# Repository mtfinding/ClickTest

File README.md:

# Automated Continuity Testing Device

## Overview

This repository contains the finalized source-code and hardware design documents of an automated hardware-tester. The projects was created as part of bachelor-thesis and is specifically designed for the Nucleo L432KC development board in combination with a propriatory harwdare expander used at my uni FHTW)  
## Features

- **Automated Continuity Testing**: The device automates the continuity testing process, reducing manual effort and increasing efficiency.
- **Terminal Interface**: A 115200baud UART terminal is available to visulaize test-results and select from certain testing-options.
- **Quick-Test Button**: A physical button that can be mapped to various test-actions via terminal commands.

## System overview

The system consists of a single PCBA project which can be broken apart in all necessary components with only little manual THT soldering required.
The main components are outlined in the image below.

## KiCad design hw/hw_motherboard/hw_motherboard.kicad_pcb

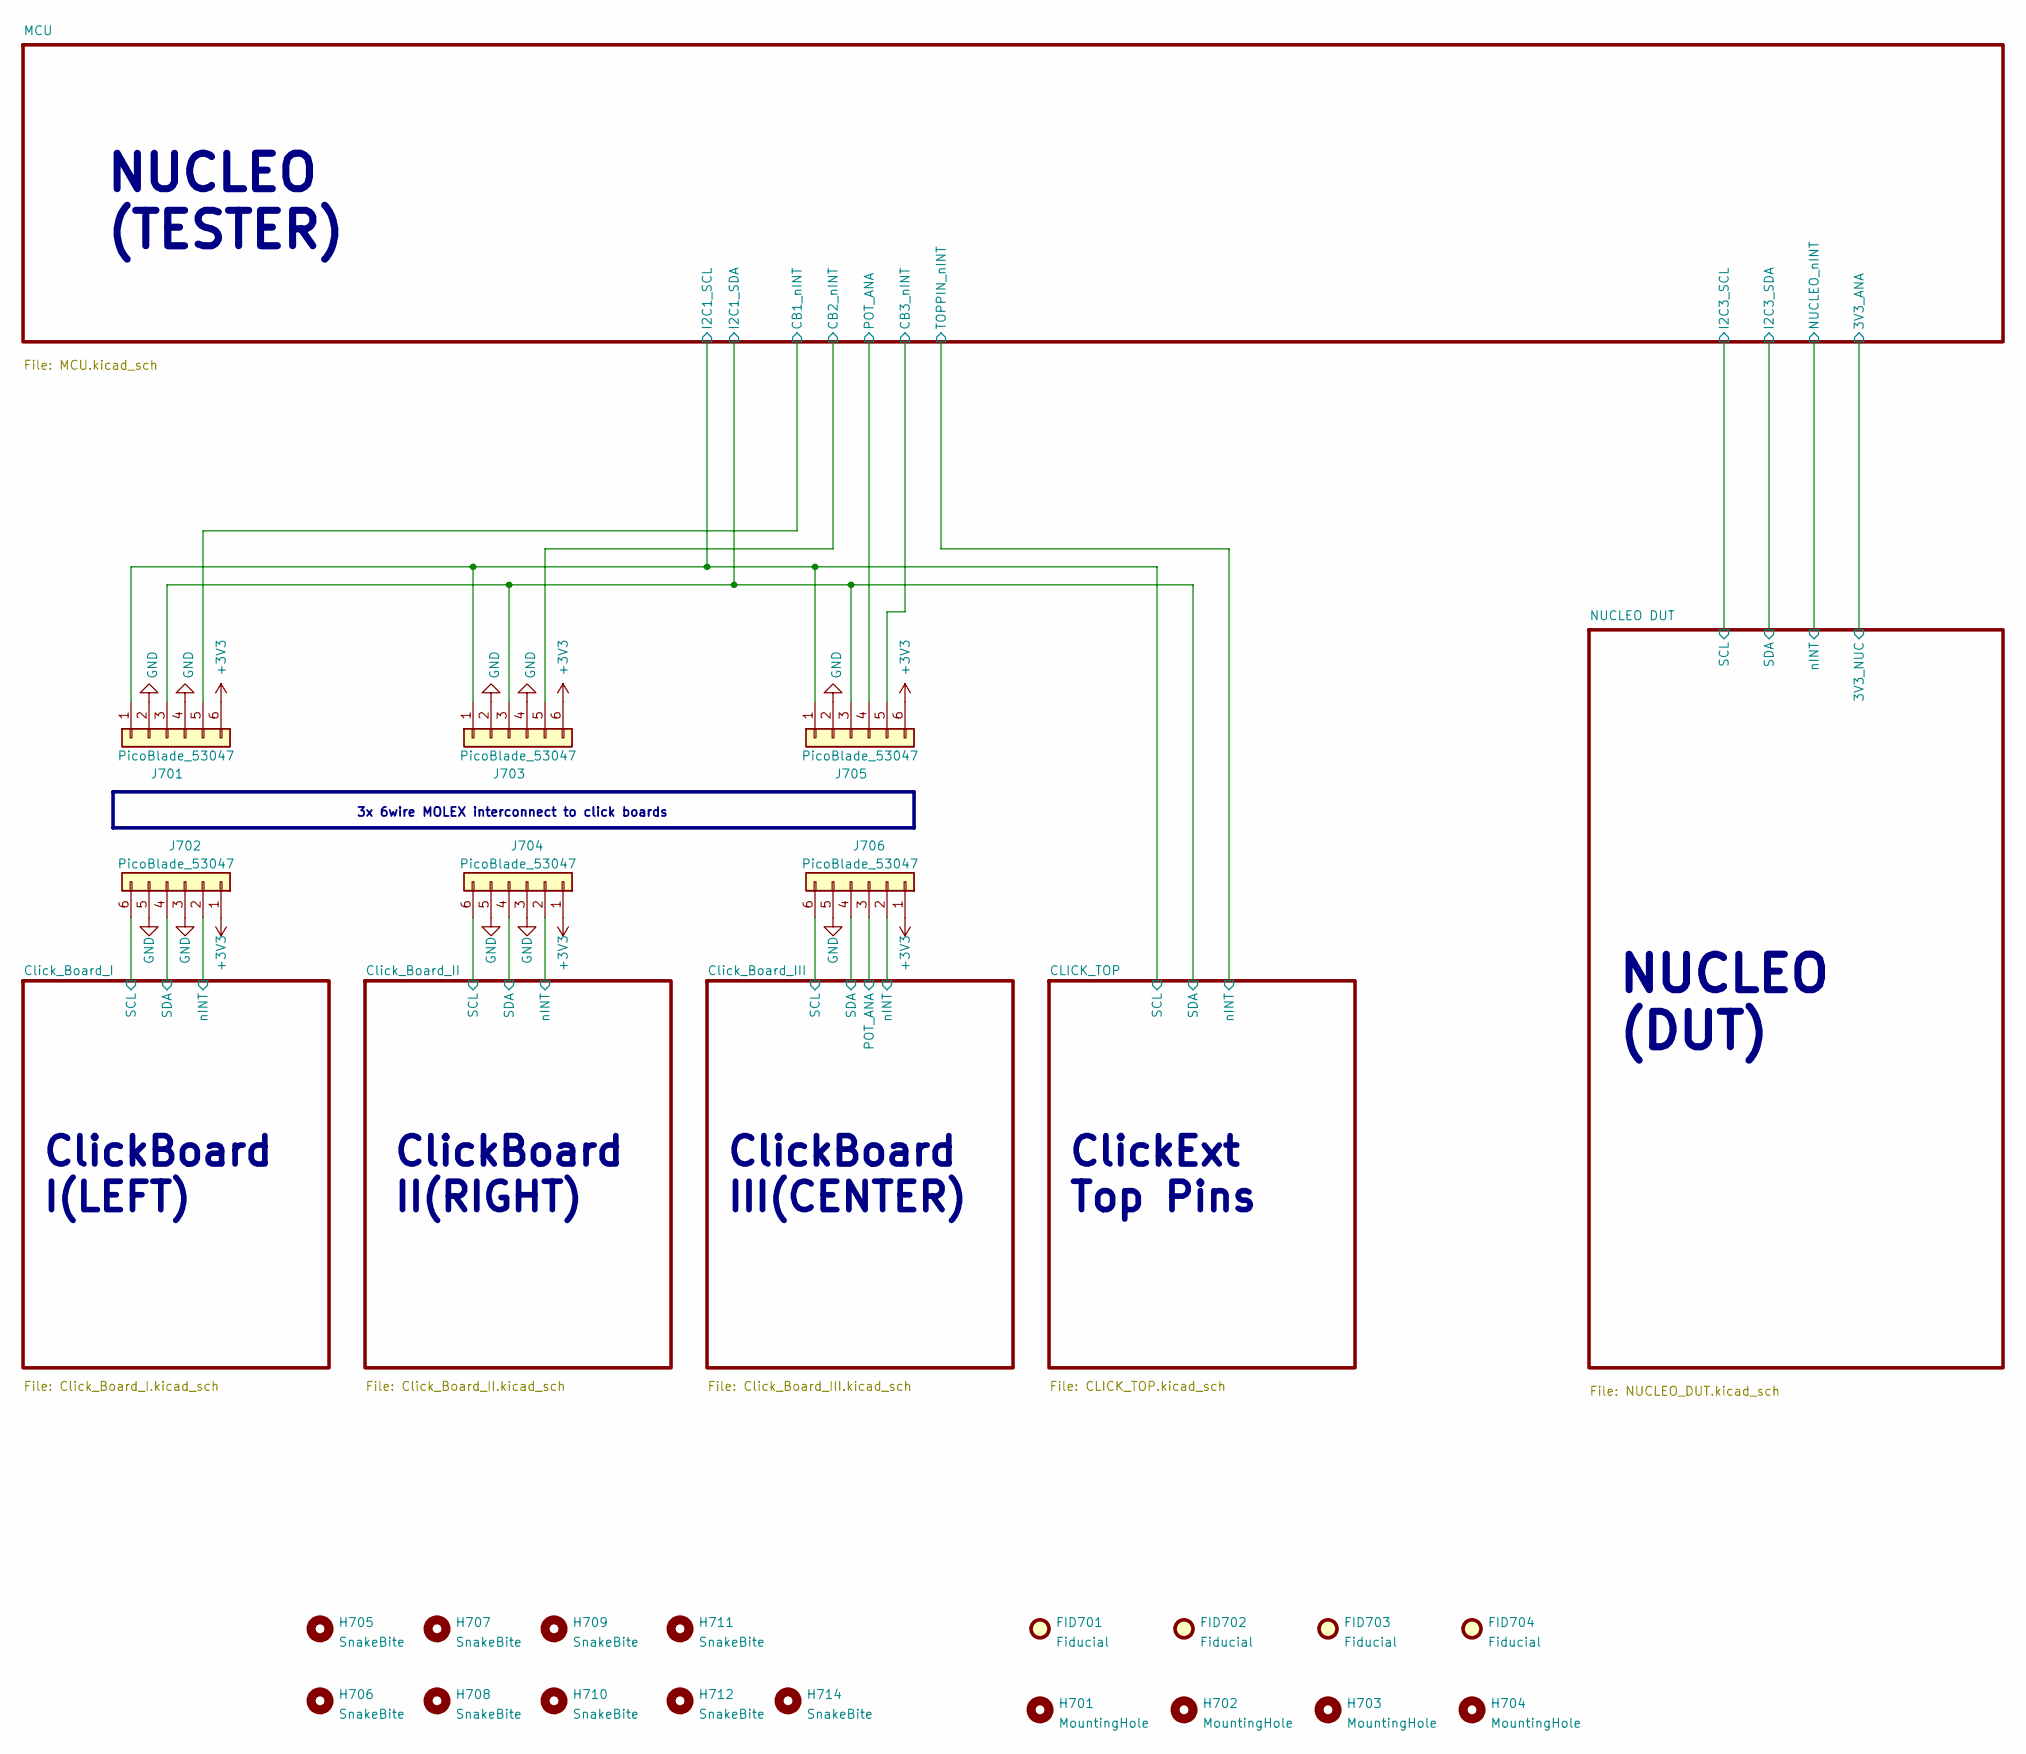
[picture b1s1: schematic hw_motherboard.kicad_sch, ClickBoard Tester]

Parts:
FID701, FID702, FID703, FID704: Fiducial; Fiducial_1mm_Mask2mm
H701, H702, H703, H704: MountingHole; MountingHole_3.2mm_M3_Pad_Via
H705, H706, H707, H708, H709, H710, H711, H712, H714: SnakeBite; JLC_SnakeBite_1.27mm
J701, J702, J703, J704, J705, J706: PicoBlade_53047; Molex_PicoBlade_53047-0610_1x06_P1.25mm_Vertical

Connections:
+3V3: J701.6, J702.1, J703.6, J704.1, J705.6, J706.1; also elsewhere on the board
/Click_Board_I/SCL: J702.6; also elsewhere on the board
/Click_Board_I/SDA: J702.4; also elsewhere on the board
/Click_Board_I/nINT: J702.2; also elsewhere on the board
/Click_Board_II/SCL: J704.6; also elsewhere on the board
/Click_Board_II/SDA: J704.4; also elsewhere on the board
/Click_Board_II/nINT: J704.2; also elsewhere on the board
/Click_Board_III/POT_ANA: J706.3; also elsewhere on the board
/Click_Board_III/SCL: J706.6; also elsewhere on the board
/Click_Board_III/SDA: J706.4; also elsewhere on the board
/Click_Board_III/nINT: J706.2; also elsewhere on the board
/MCU/MCU_PA9: J701.1, J703.1, J705.1; also elsewhere on the board
/MCU/MCU_PA10: J701.3, J703.3, J705.3; also elsewhere on the board
/MCU/MCU_PB6: J701.5, J703.5, J705.5; also elsewhere on the board
/MCU/POT_ANA: J705.4; also elsewhere on the board
GND: J701.2, J701.4, J702.3, J702.5, J703.2, J703.4, J704.3, J704.5, J705.2, J706.5; also elsewhere on the board

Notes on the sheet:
3x 6wire MOLEX interconnect to click boards
NUCLEO (DUT)
ClickBoard I(LEFT)
ClickExt Top Pins
ClickBoard III(CENTER)
NUCLEO (TESTER)
ClickBoard II(RIGHT)

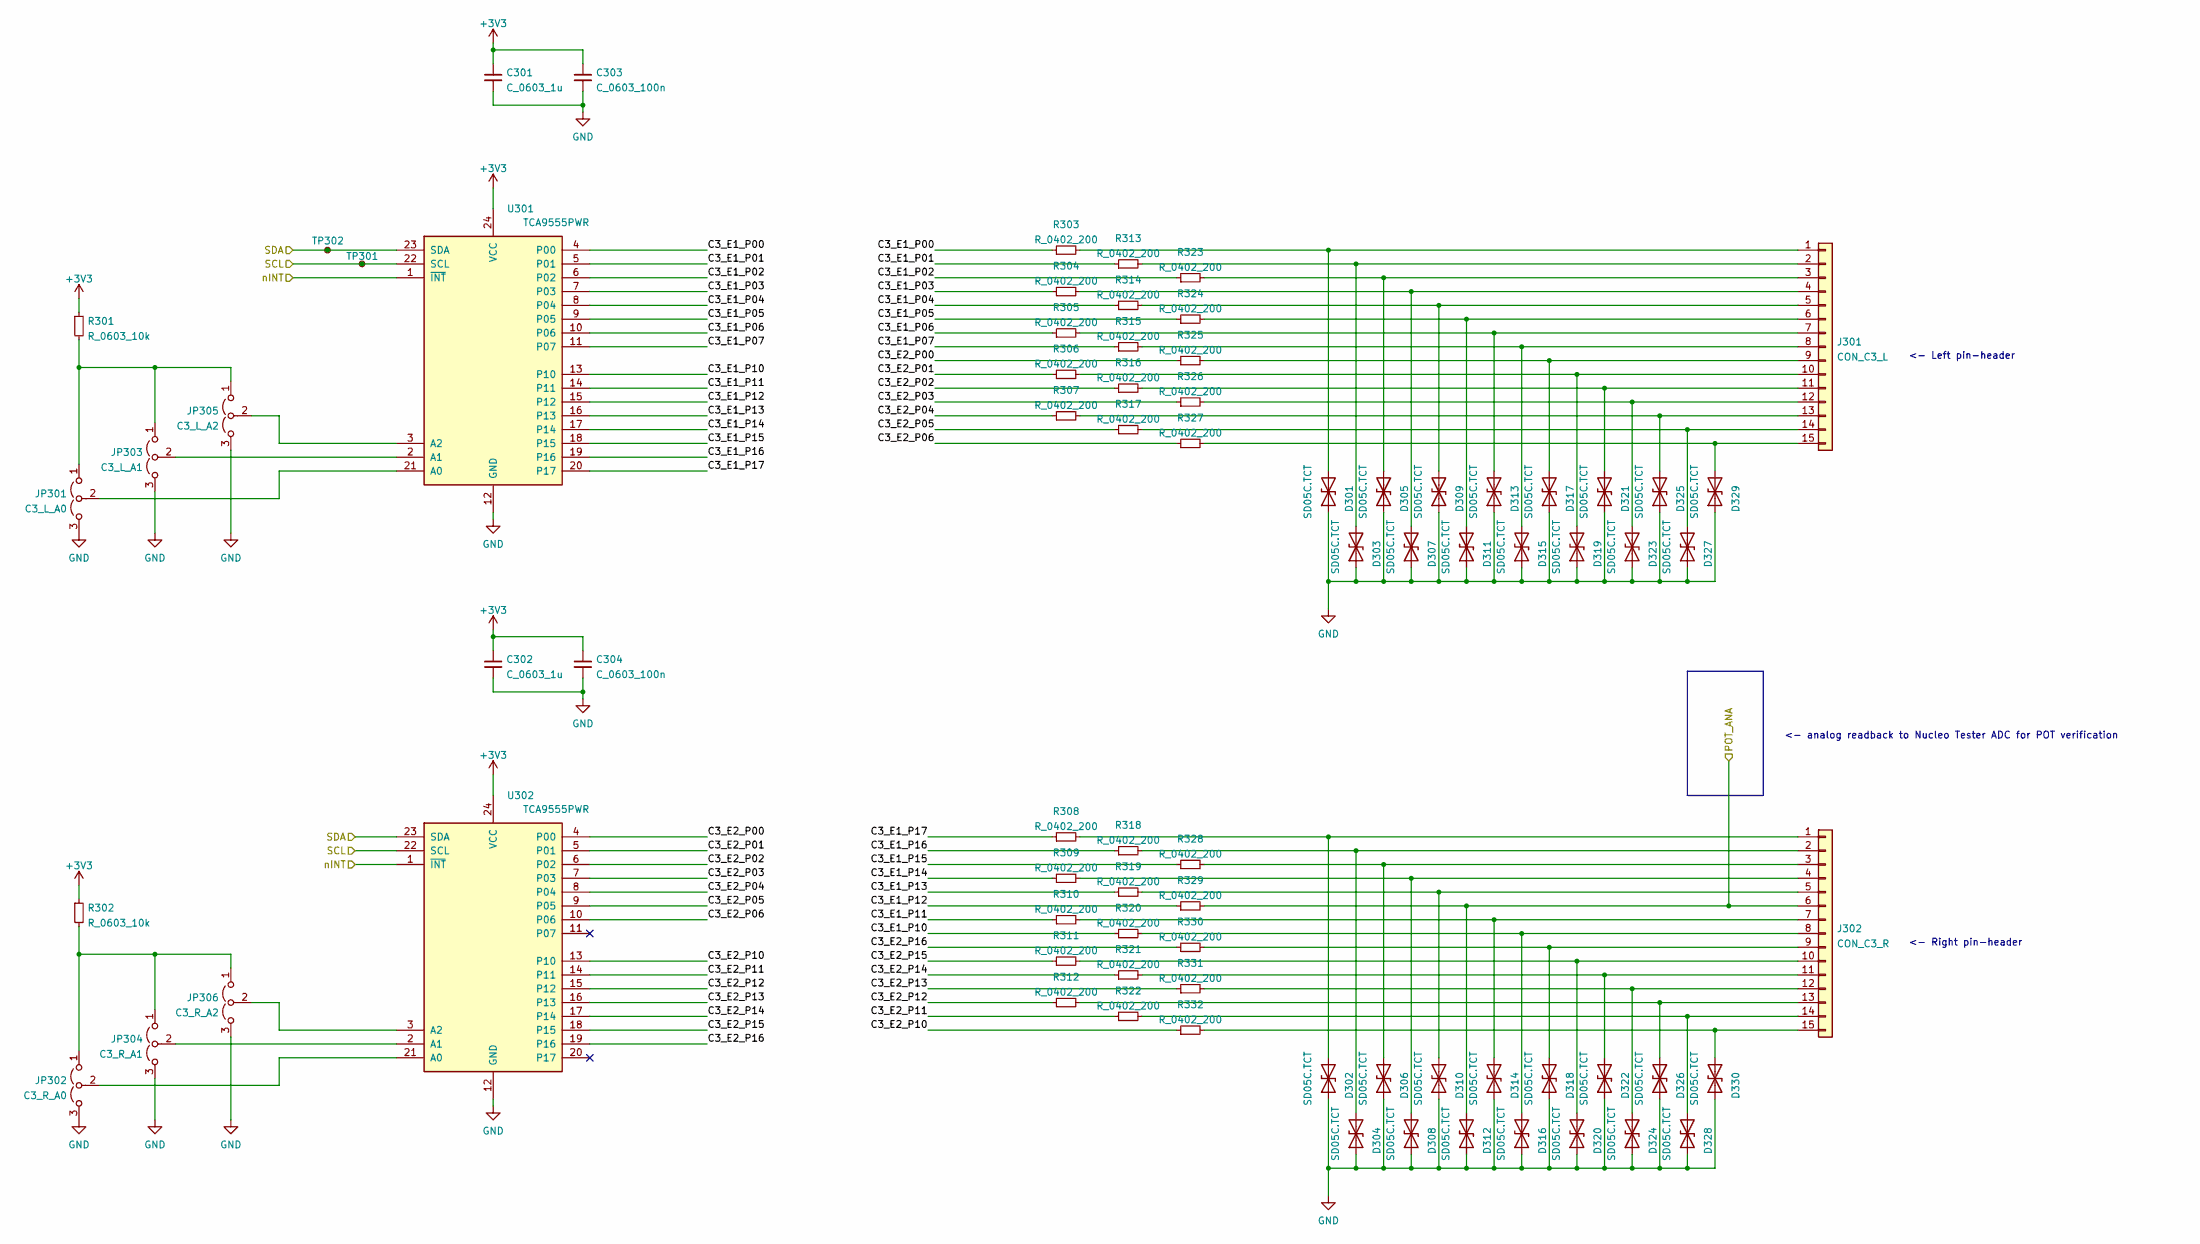
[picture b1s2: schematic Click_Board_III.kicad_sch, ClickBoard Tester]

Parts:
C301, C302: C_0603_1u; C_0603_1608Metric; LCSC Part # C15849
C303, C304: C_0603_100n; C_0603_1608Metric; LCSC Part # C14663
D301, D302, D303, D304, D305, D306, D307, D308, D309, D310, D311, D312, D313, D314, D315, D316, D317, D318, D319, D320, D321, D322, D323, D324, D325, D326, D327, D328, D329, D330: SD05C.TCT; D_SOD-323_HandSoldering; LCSC Part # C85200
J301: CON_C3_L; PinHeader_1x15_P2.54mm_Vertical
J302: CON_C3_R; PinHeader_1x15_P2.54mm_Vertical
JP301: C3_L_A0; SolderJumper-3_P1.3mm_Open_RoundedPad1.0x1.5mm
JP302: C3_R_A0; SolderJumper-3_P1.3mm_Open_RoundedPad1.0x1.5mm
JP303: C3_L_A1; SolderJumper-3_P1.3mm_Open_RoundedPad1.0x1.5mm
JP304: C3_R_A1; SolderJumper-3_P1.3mm_Open_RoundedPad1.0x1.5mm
JP305: C3_L_A2; SolderJumper-3_P1.3mm_Open_RoundedPad1.0x1.5mm
JP306: C3_R_A2; SolderJumper-3_P1.3mm_Open_RoundedPad1.0x1.5mm
R301, R302: R_0603_10k; R_0603_1608Metric; LCSC Part # C25804
R303, R304, R305, R306, R307, R308, R309, R310, R311, R312, R313, R314, R315, R316, R317, R318, R319, R320, R321, R322, R323, R324, R325, R326, R327, R328, R329, R330, R331, R332: R_0402_200; R_0402_1005Metric; LCSC Part # C25087
TP301, TP302: TestPoint_Small; TestPoint_Pad_D1.0mm
U301, U302: TCA9555PWR; TSSOP-24_4.4x7.8mm_P0.65mm

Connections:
+3V3: C301.1, C302.1, C303.1, C304.1, R301.1, R302.1, U301.24 (VCC), U302.24 (VCC); also elsewhere on the board
/Click_Board_III/C3_E1_P00: R303.1, U301.4 (P00)
/Click_Board_III/C3_E1_P01: R313.1, U301.5 (P01)
/Click_Board_III/C3_E1_P02: R323.1, U301.6 (P02)
/Click_Board_III/C3_E1_P03: R304.1, U301.7 (P03)
/Click_Board_III/C3_E1_P04: R314.1, U301.8 (P04)
/Click_Board_III/C3_E1_P05: R324.1, U301.9 (P05)
/Click_Board_III/C3_E1_P06: R305.1, U301.10 (P06)
/Click_Board_III/C3_E1_P07: R315.1, U301.11 (P07)
/Click_Board_III/C3_E1_P10: R320.1, U301.13 (P10)
/Click_Board_III/C3_E1_P11: R310.1, U301.14 (P11)
/Click_Board_III/C3_E1_P12: R329.1, U301.15 (P12)
/Click_Board_III/C3_E1_P13: R319.1, U301.16 (P13)
/Click_Board_III/C3_E1_P14: R309.1, U301.17 (P14)
/Click_Board_III/C3_E1_P15: R328.1, U301.18 (P15)
/Click_Board_III/C3_E1_P16: R318.1, U301.19 (P16)
/Click_Board_III/C3_E1_P17: R308.1, U301.20 (P17)
/Click_Board_III/C3_E2_P00: R325.1, U302.4 (P00)
/Click_Board_III/C3_E2_P01: R306.1, U302.5 (P01)
/Click_Board_III/C3_E2_P02: R316.1, U302.6 (P02)
/Click_Board_III/C3_E2_P03: R326.1, U302.7 (P03)
/Click_Board_III/C3_E2_P04: R307.1, U302.8 (P04)
/Click_Board_III/C3_E2_P05: R317.1, U302.9 (P05)
/Click_Board_III/C3_E2_P06: R327.1, U302.10 (P06)
/Click_Board_III/C3_E2_P10: R332.1, U302.13 (P10)
/Click_Board_III/C3_E2_P11: R322.1, U302.14 (P11)
/Click_Board_III/C3_E2_P12: R312.1, U302.15 (P12)
/Click_Board_III/C3_E2_P13: R331.1, U302.16 (P13)
/Click_Board_III/C3_E2_P14: R321.1, U302.17 (P14)
/Click_Board_III/C3_E2_P15: R311.1, U302.18 (P15)
/Click_Board_III/C3_E2_P16: R330.1, U302.19 (P16)
/Click_Board_III/POT_ANA: D312.2 (A2), J302.6, R329.2; also elsewhere on the board
/Click_Board_III/SCL: TP301.1, U301.22 (SCL), U302.22 (SCL); also elsewhere on the board
/Click_Board_III/SDA: TP302.1, U301.23 (SDA), U302.23 (SDA); also elsewhere on the board
/Click_Board_III/nINT: U301.1 (~INT), U302.1 (~INT); also elsewhere on the board
GND: C301.2, C302.2, C303.2, C304.2, D301.1 (A1), D302.1 (A1), D303.1 (A1), D304.1 (A1), D305.1 (A1), D306.1 (A1), D307.1 (A1), D308.1 (A1), D309.1 (A1), D310.1 (A1), D311.1 (A1), D312.1 (A1), D313.1 (A1), D314.1 (A1), D315.1 (A1), D316.1 (A1), D317.1 (A1), D318.1 (A1), D319.1 (A1), D320.1 (A1), D321.1 (A1), D322.1 (A1), D323.1 (A1), D324.1 (A1), D325.1 (A1), D326.1 (A1), D327.1 (A1), D328.1 (A1), D329.1 (A1), D330.1 (A1), JP301.3 (B), JP302.3 (B), JP303.3 (B), JP304.3 (B), JP305.3 (B), JP306.3 (B), U301.12 (GND), U302.12 (GND); also elsewhere on the board
unnamed: D301.2 (A2), J301.1, R303.2
unnamed: D302.2 (A2), J302.1, R308.2
unnamed: D303.2 (A2), J301.2, R313.2
unnamed: D304.2 (A2), J302.2, R318.2
unnamed: D305.2 (A2), J301.3, R323.2
unnamed: D306.2 (A2), J302.3, R328.2
unnamed: D307.2 (A2), J301.4, R304.2
unnamed: D308.2 (A2), J302.4, R309.2
unnamed: D309.2 (A2), J301.5, R314.2
unnamed: D310.2 (A2), J302.5, R319.2
unnamed: D311.2 (A2), J301.6, R324.2
unnamed: D313.2 (A2), J301.7, R305.2
unnamed: D314.2 (A2), J302.7, R310.2
unnamed: D315.2 (A2), J301.8, R315.2
unnamed: D316.2 (A2), J302.8, R320.2
unnamed: D317.2 (A2), J301.9, R325.2
unnamed: D318.2 (A2), J302.9, R330.2
unnamed: D319.2 (A2), J301.10, R306.2
unnamed: D320.2 (A2), J302.10, R311.2
unnamed: D321.2 (A2), J301.11, R316.2
unnamed: D322.2 (A2), J302.11, R321.2
unnamed: D323.2 (A2), J301.12, R326.2
unnamed: D324.2 (A2), J302.12, R331.2
unnamed: D325.2 (A2), J301.13, R307.2
unnamed: D326.2 (A2), J302.13, R312.2
unnamed: D327.2 (A2), J301.14, R317.2
unnamed: D328.2 (A2), J302.14, R322.2
unnamed: D329.2 (A2), J301.15, R327.2
unnamed: D330.2 (A2), J302.15, R332.2
unnamed: JP301.1 (A), JP303.1 (A), JP305.1 (A), R301.2
unnamed: JP301.2 (C), U301.21 (A0)
unnamed: JP302.1 (A), JP304.1 (A), JP306.1 (A), R302.2
unnamed: JP302.2 (C), U302.21 (A0)
unnamed: JP303.2 (C), U301.2 (A1)
unnamed: JP304.2 (C), U302.2 (A1)
unnamed: JP305.2 (C), U301.3 (A2)
unnamed: JP306.2 (C), U302.3 (A2)

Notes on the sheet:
<- Right pin-header
<- Left pin-header
<- analog readback to Nucleo Tester ADC for POT verification

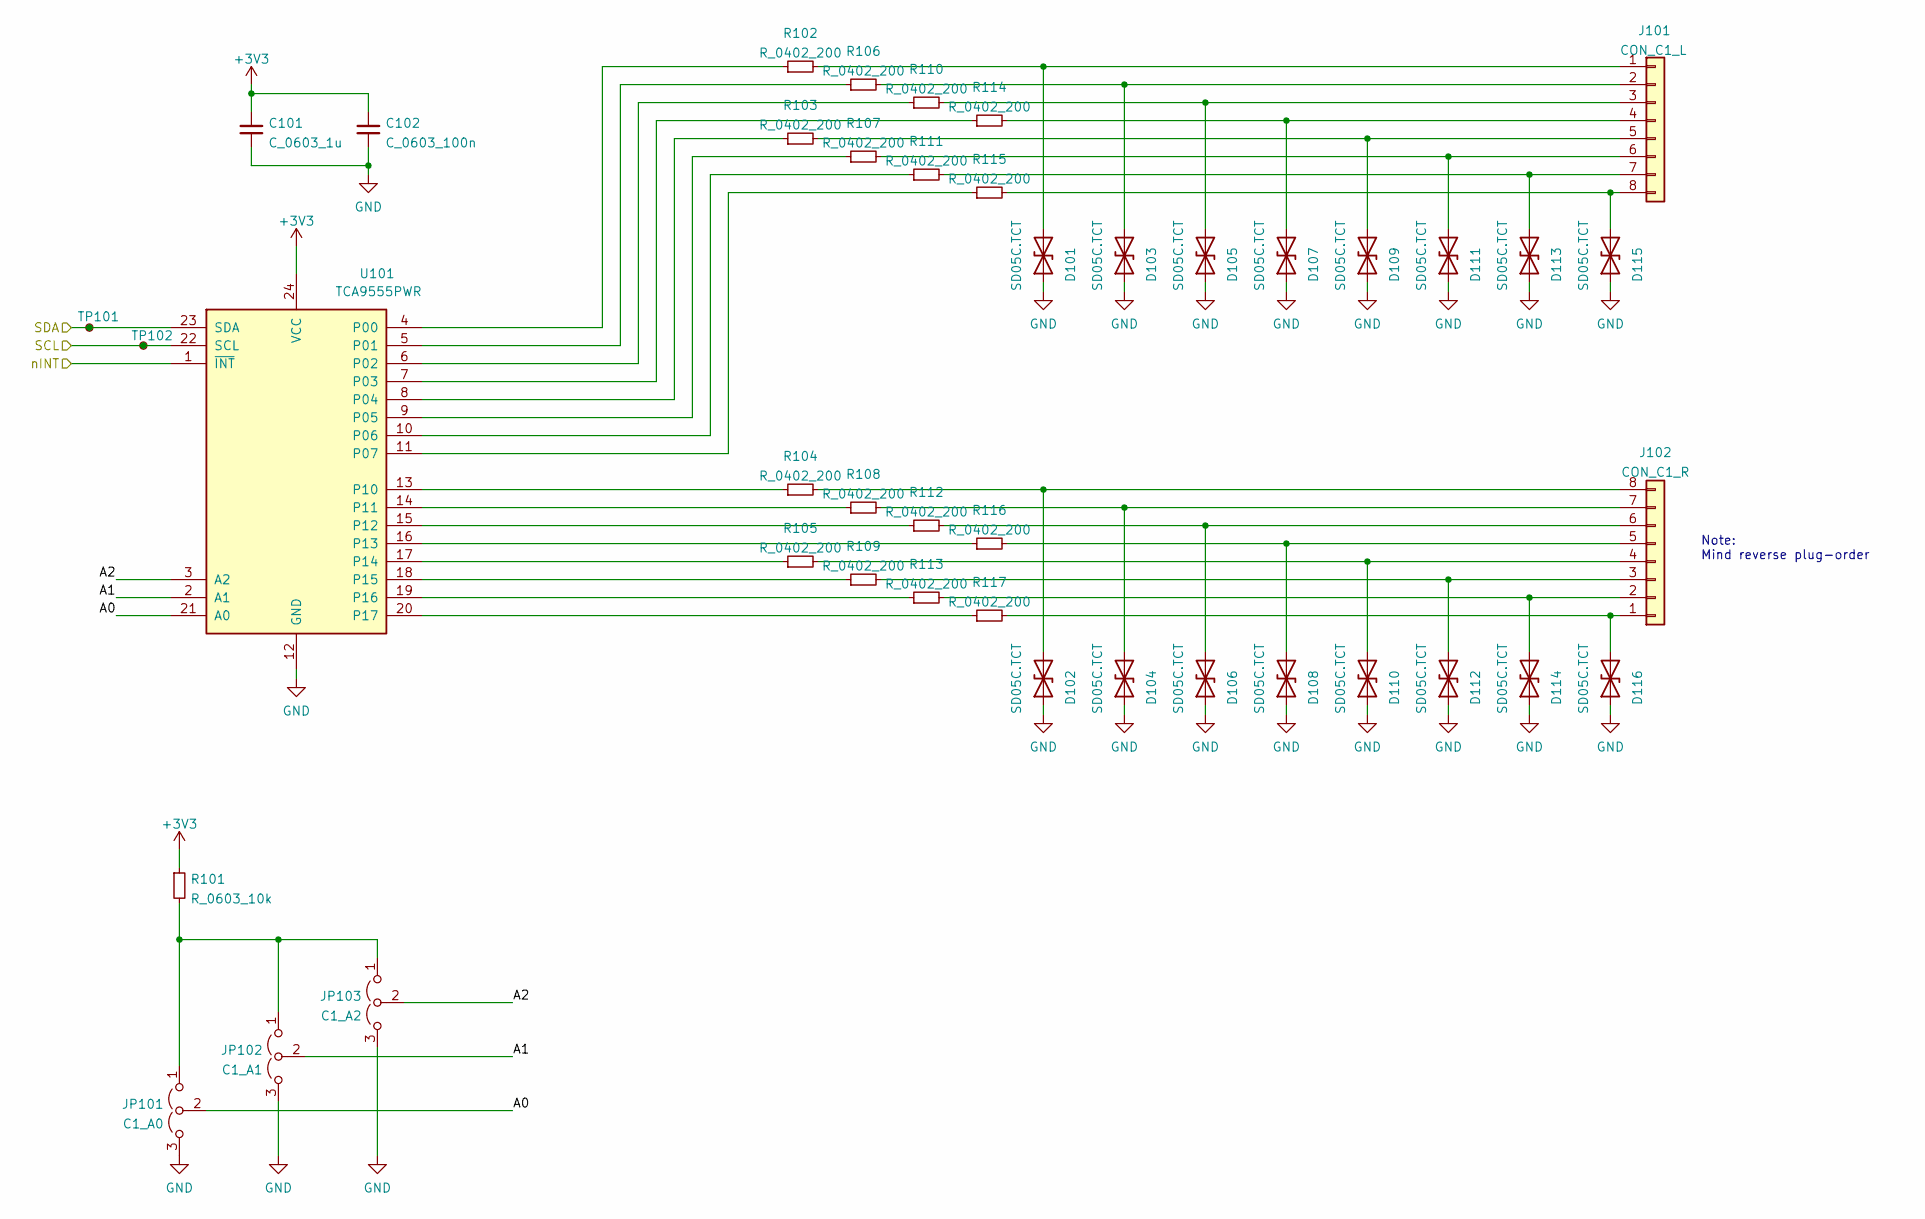
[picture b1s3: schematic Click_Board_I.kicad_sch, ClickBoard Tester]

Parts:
C101: C_0603_1u; C_0603_1608Metric; LCSC Part # C15849
C102: C_0603_100n; C_0603_1608Metric; LCSC Part # C14663
D101, D102, D103, D104, D105, D106, D107, D108, D109, D110, D111, D112, D113, D114, D115, D116: SD05C.TCT; D_SOD-323_HandSoldering; LCSC Part # C85200
J101: CON_C1_L; PinHeader_1x08_P2.54mm_Vertical
J102: CON_C1_R; PinHeader_1x08_P2.54mm_Vertical
JP101: C1_A0; SolderJumper-3_P1.3mm_Open_RoundedPad1.0x1.5mm
JP102: C1_A1; SolderJumper-3_P1.3mm_Open_RoundedPad1.0x1.5mm
JP103: C1_A2; SolderJumper-3_P1.3mm_Open_RoundedPad1.0x1.5mm
R101: R_0603_10k; R_0603_1608Metric; LCSC Part # C25804
R102, R103, R104, R105, R106, R107, R108, R109, R110, R111, R112, R113, R114, R115, R116, R117: R_0402_200; R_0402_1005Metric; LCSC Part # C25087
TP101, TP102: TestPoint_Small; TestPoint_Pad_D1.0mm
U101: TCA9555PWR; TSSOP-24_4.4x7.8mm_P0.65mm

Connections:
+3V3: C101.1, C102.1, R101.1, U101.24 (VCC); also elsewhere on the board
/Click_Board_I/A0: JP101.2 (C), U101.21 (A0)
/Click_Board_I/A1: JP102.2 (C), U101.2 (A1)
/Click_Board_I/A2: JP103.2 (C), U101.3 (A2)
/Click_Board_I/SCL: TP102.1, U101.22 (SCL); also elsewhere on the board
/Click_Board_I/SDA: TP101.1, U101.23 (SDA); also elsewhere on the board
/Click_Board_I/nINT: U101.1 (~INT); also elsewhere on the board
GND: C101.2, C102.2, D101.1 (A1), D102.1 (A1), D103.1 (A1), D104.1 (A1), D105.1 (A1), D106.1 (A1), D107.1 (A1), D108.1 (A1), D109.1 (A1), D110.1 (A1), D111.1 (A1), D112.1 (A1), D113.1 (A1), D114.1 (A1), D115.1 (A1), D116.1 (A1), JP101.3 (B), JP102.3 (B), JP103.3 (B), U101.12 (GND); also elsewhere on the board
unnamed: D101.2 (A2), J101.1, R102.2
unnamed: D102.2 (A2), J102.8, R104.2
unnamed: D103.2 (A2), J101.2, R106.2
unnamed: D104.2 (A2), J102.7, R108.2
unnamed: D105.2 (A2), J101.3, R110.2
unnamed: D106.2 (A2), J102.6, R112.2
unnamed: D107.2 (A2), J101.4, R114.2
unnamed: D108.2 (A2), J102.5, R116.2
unnamed: D109.2 (A2), J101.5, R103.2
unnamed: D110.2 (A2), J102.4, R105.2
unnamed: D111.2 (A2), J101.6, R107.2
unnamed: D112.2 (A2), J102.3, R109.2
unnamed: D113.2 (A2), J101.7, R111.2
unnamed: D114.2 (A2), J102.2, R113.2
unnamed: D115.2 (A2), J101.8, R115.2
unnamed: D116.2 (A2), J102.1, R117.2
unnamed: JP101.1 (A), JP102.1 (A), JP103.1 (A), R101.2
unnamed: R102.1, U101.4 (P00)
unnamed: R103.1, U101.8 (P04)
unnamed: R104.1, U101.13 (P10)
unnamed: R105.1, U101.17 (P14)
unnamed: R106.1, U101.5 (P01)
unnamed: R107.1, U101.9 (P05)
unnamed: R108.1, U101.14 (P11)
unnamed: R109.1, U101.18 (P15)
unnamed: R110.1, U101.6 (P02)
unnamed: R111.1, U101.10 (P06)
unnamed: R112.1, U101.15 (P12)
unnamed: R113.1, U101.19 (P16)
unnamed: R114.1, U101.7 (P03)
unnamed: R115.1, U101.11 (P07)
unnamed: R116.1, U101.16 (P13)
unnamed: R117.1, U101.20 (P17)

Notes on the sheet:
Note: Mind reverse plug-order

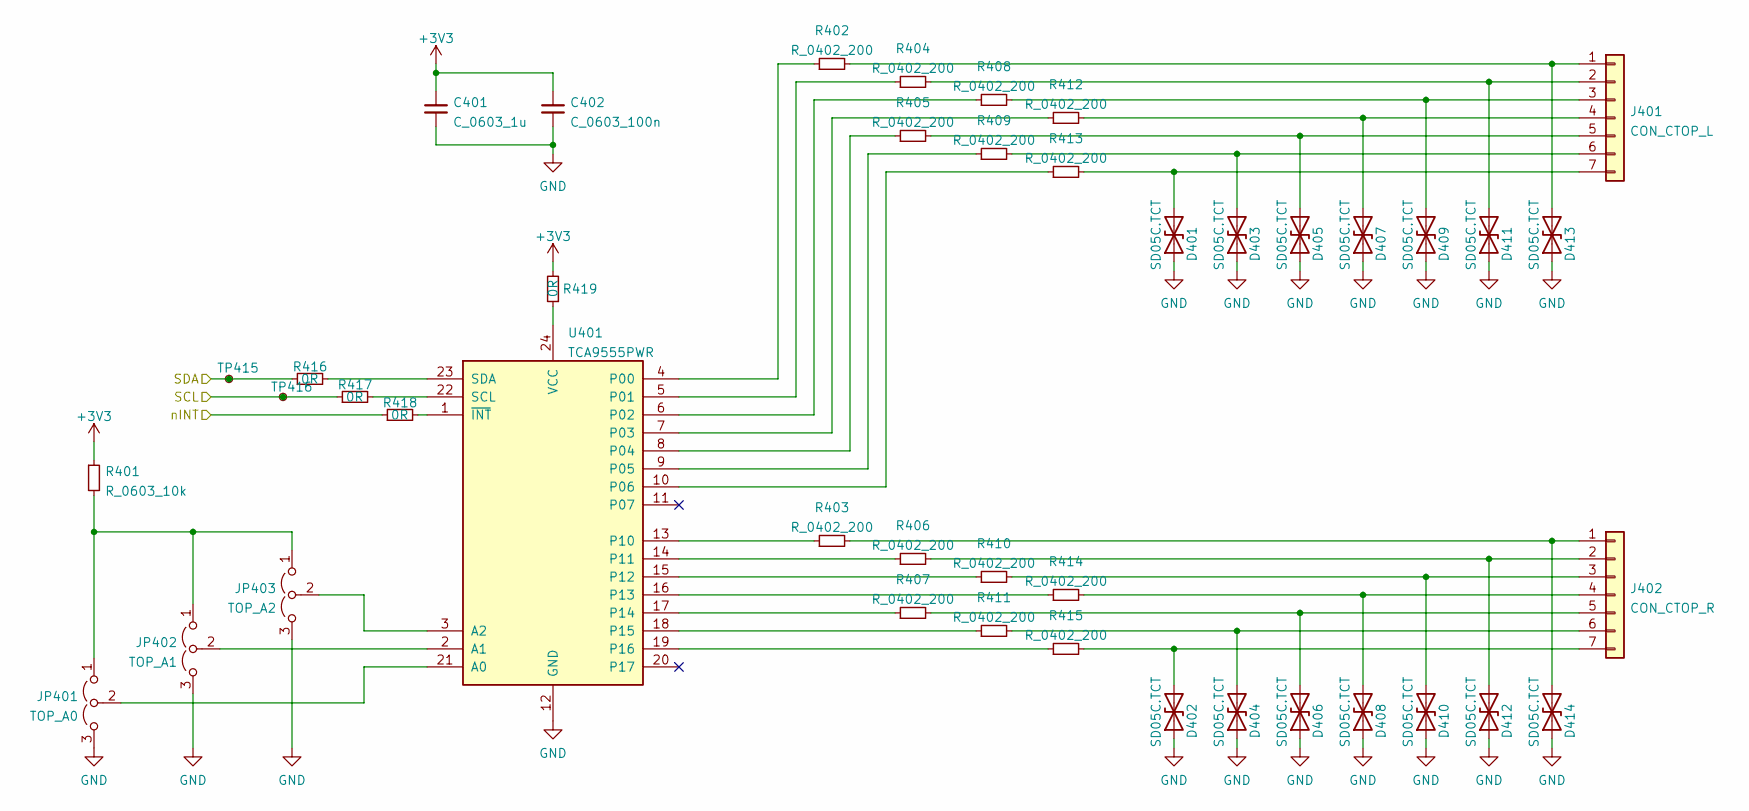
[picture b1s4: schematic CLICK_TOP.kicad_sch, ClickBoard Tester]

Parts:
C401: C_0603_1u; C_0603_1608Metric; LCSC Part # C15849
C402: C_0603_100n; C_0603_1608Metric; LCSC Part # C14663
D401, D402, D403, D404, D405, D406, D407, D408, D409, D410, D411, D412, D413, D414: SD05C.TCT; D_SOD-323_HandSoldering; LCSC Part # C85200
J401: CON_CTOP_L; PinHeader_1x07_P2.54mm_Vertical
J402: CON_CTOP_R; PinHeader_1x07_P2.54mm_Vertical
JP401: TOP_A0; SolderJumper-3_P1.3mm_Open_RoundedPad1.0x1.5mm
JP402: TOP_A1; SolderJumper-3_P1.3mm_Open_RoundedPad1.0x1.5mm
JP403: TOP_A2; SolderJumper-3_P1.3mm_Open_RoundedPad1.0x1.5mm
R401: R_0603_10k; R_0603_1608Metric; LCSC Part # C25804
R402, R403, R404, R405, R406, R407, R408, R409, R410, R411, R412, R413, R414, R415: R_0402_200; R_0402_1005Metric; LCSC Part # C25087
R416, R417, R418, R419: 0R; R_0603_1608Metric_Pad0.98x0.95mm_HandSolder; LCSC Part # C21189
TP415, TP416: TestPoint_Small; TestPoint_Pad_D1.0mm
U401: TCA9555PWR; TSSOP-24_4.4x7.8mm_P0.65mm

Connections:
+3V3: C401.1, C402.1, R401.1, R419.2; also elsewhere on the board
/MCU/MCU_PA9: R417.1, TP416.1; also elsewhere on the board
/MCU/MCU_PA10: R416.1, TP415.1; also elsewhere on the board
/MCU/MCU_PB6: R418.1; also elsewhere on the board
GND: C401.2, C402.2, D401.1 (A1), D402.1 (A1), D403.1 (A1), D404.1 (A1), D405.1 (A1), D406.1 (A1), D407.1 (A1), D408.1 (A1), D409.1 (A1), D410.1 (A1), D411.1 (A1), D412.1 (A1), D413.1 (A1), D414.1 (A1), JP401.3 (B), JP402.3 (B), JP403.3 (B), U401.12 (GND); also elsewhere on the board
unnamed: D401.2 (A2), J401.7, R413.2
unnamed: D402.2 (A2), J402.7, R415.2
unnamed: D403.2 (A2), J401.6, R409.2
unnamed: D404.2 (A2), J402.6, R411.2
unnamed: D405.2 (A2), J401.5, R405.2
unnamed: D406.2 (A2), J402.5, R407.2
unnamed: D407.2 (A2), J401.4, R412.2
unnamed: D408.2 (A2), J402.4, R414.2
unnamed: D409.2 (A2), J401.3, R408.2
unnamed: D410.2 (A2), J402.3, R410.2
unnamed: D411.2 (A2), J401.2, R404.2
unnamed: D412.2 (A2), J402.2, R406.2
unnamed: D413.2 (A2), J401.1, R402.2
unnamed: D414.2 (A2), J402.1, R403.2
unnamed: JP401.1 (A), JP402.1 (A), JP403.1 (A), R401.2
unnamed: JP401.2 (C), U401.21 (A0)
unnamed: JP402.2 (C), U401.2 (A1)
unnamed: JP403.2 (C), U401.3 (A2)
unnamed: R402.1, U401.4 (P00)
unnamed: R403.1, U401.13 (P10)
unnamed: R404.1, U401.5 (P01)
unnamed: R405.1, U401.8 (P04)
unnamed: R406.1, U401.14 (P11)
unnamed: R407.1, U401.17 (P14)
unnamed: R408.1, U401.6 (P02)
unnamed: R409.1, U401.9 (P05)
unnamed: R410.1, U401.15 (P12)
unnamed: R411.1, U401.18 (P15)
unnamed: R412.1, U401.7 (P03)
unnamed: R413.1, U401.10 (P06)
unnamed: R414.1, U401.16 (P13)
unnamed: R415.1, U401.19 (P16)
unnamed: R416.2, U401.23 (SDA)
unnamed: R417.2, U401.22 (SCL)
unnamed: R418.2, U401.1 (~INT)
unnamed: R419.1, U401.24 (VCC)

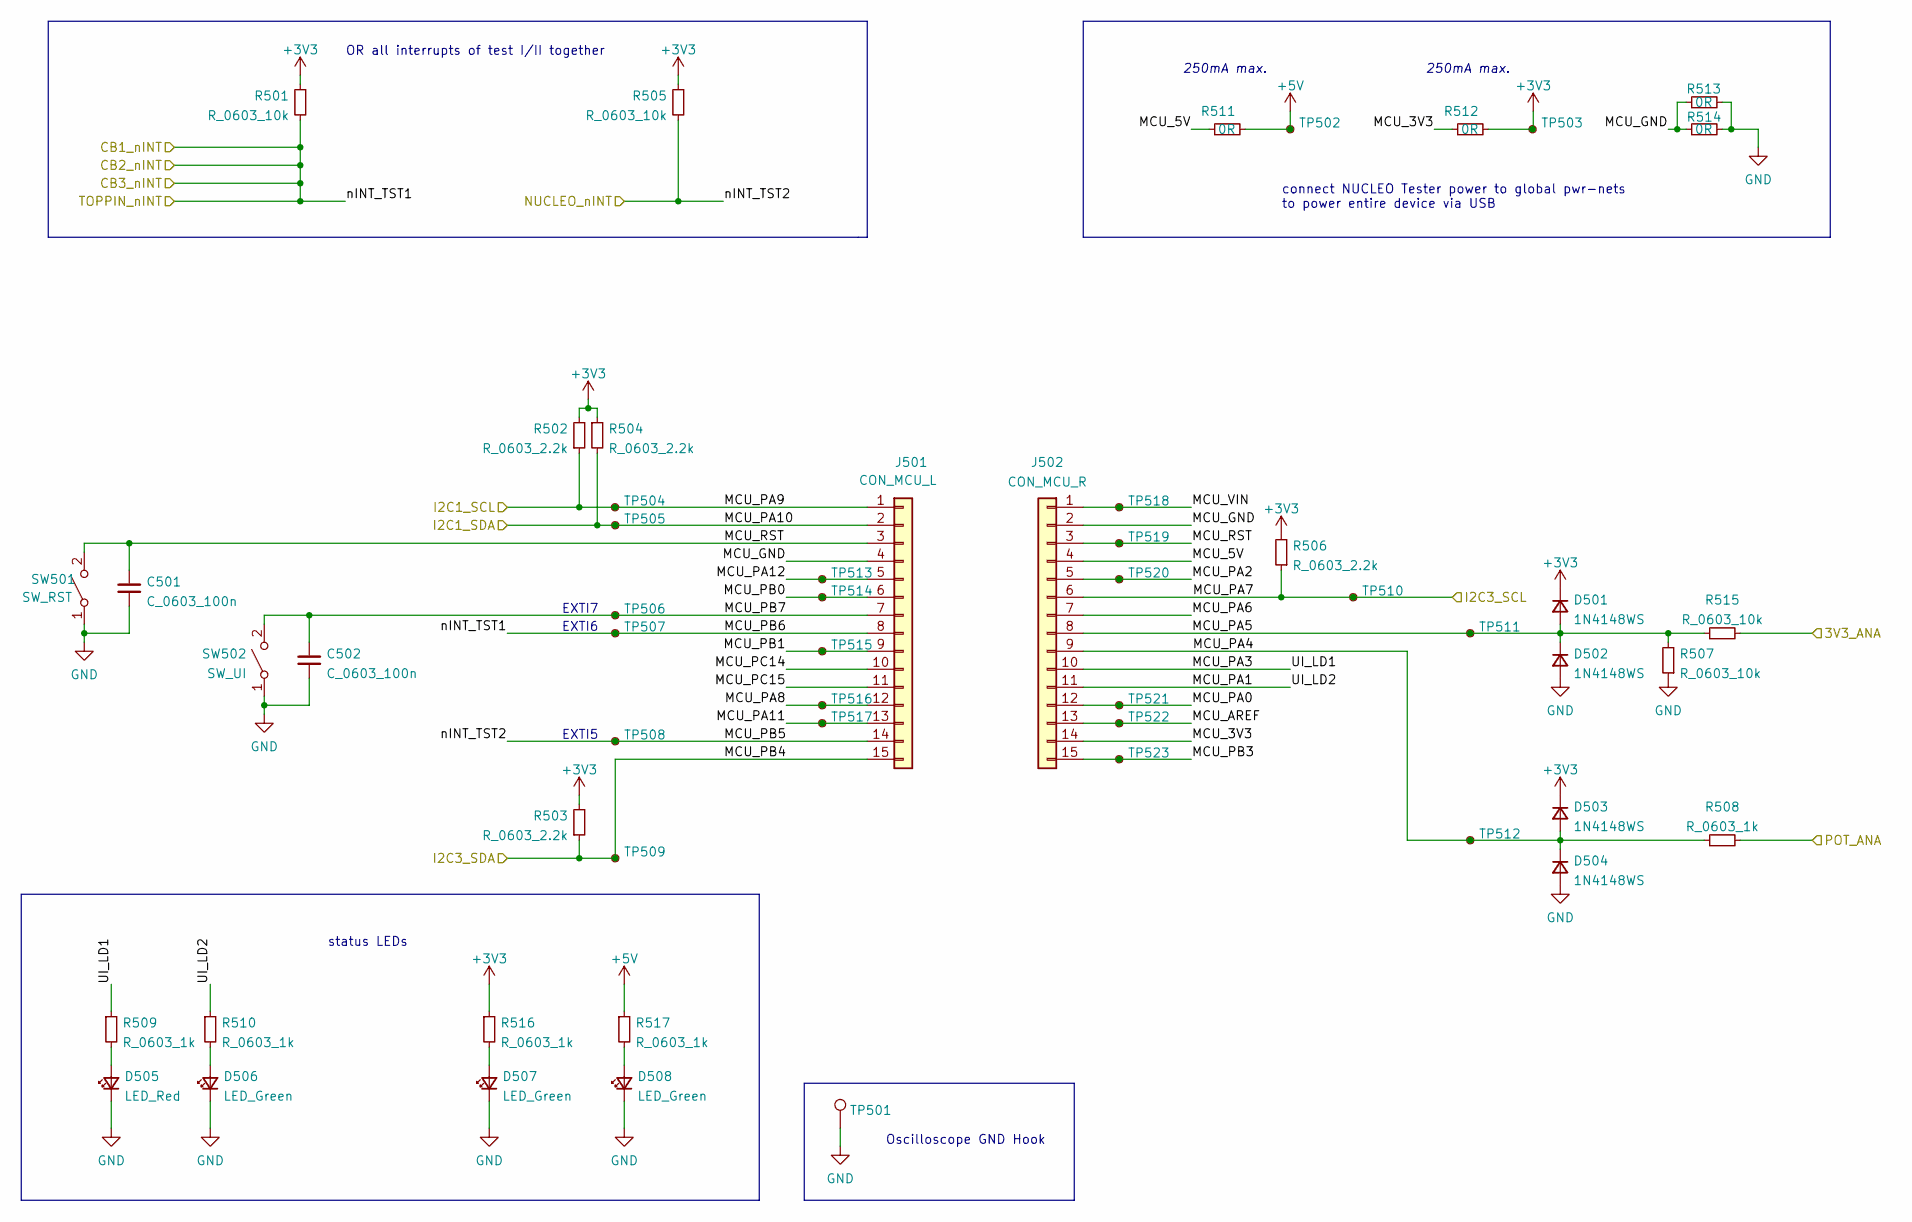
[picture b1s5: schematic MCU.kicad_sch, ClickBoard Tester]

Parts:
C501, C502: C_0603_100n; C_0603_1608Metric; LCSC Part # C14663
D501, D502, D503, D504: 1N4148WS; D_SOD-323F; LCSC Part # C2128
D505: LED_Red; LED_0603_1608Metric; LCSC Part # C2286
D506, D507, D508: LED_Green; LED_0603_1608Metric; LCSC Part # C72043
J501: CON_MCU_L; PinSocket_1x15_P2.54mm_Vertical
J502: CON_MCU_R; PinSocket_1x15_P2.54mm_Vertical
R501, R505, R507, R515: R_0603_10k; R_0603_1608Metric; LCSC Part # C25804
R502, R503, R504, R506: R_0603_2.2k; R_0603_1608Metric; LCSC Part # C4190
R508, R509, R510, R516, R517: R_0603_1k; R_0603_1608Metric; LCSC Part # C21190
R511, R512, R513, R514: 0R; R_0603_1608Metric_Pad0.98x0.95mm_HandSolder; LCSC Part # C21189
SW501: SW_RST; SW_PUSH_6mm
SW502: SW_UI; SW_PUSH_6mm
TP501: TestPoint; TestPoint_Keystone_5000-5004_Miniature
TP502, TP503, TP504, TP505, TP506, TP507, TP508, TP509, TP510, TP511, TP512, TP513, TP514, TP515, TP516, TP517, TP518, TP519, TP520, TP521, TP522, TP523: TestPoint_Small; TestPoint_Pad_D1.0mm

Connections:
+3V3: D501.1 (K), D503.1 (K), R501.1, R502.2, R503.2, R504.1, R505.1, R506.2, R512.2, R516.1, TP503.1; also elsewhere on the board
+5V: R511.2, R517.1, TP502.1; also elsewhere on the board
/MCU/MCU_3V3: J502.14, R512.1
/MCU/MCU_5V: J502.4, R511.1
/MCU/MCU_AREF: J502.13, TP522.1
/MCU/MCU_GND: J501.4, J502.2, R513.1, R514.1
/MCU/MCU_PA0: J502.12, TP521.1
/MCU/MCU_PA1: J502.11, R510.1
/MCU/MCU_PA2: J502.5, TP520.1
/MCU/MCU_PA3: J502.10, R509.1
/MCU/MCU_PA4: D503.2 (A), D504.1 (K), J502.9, R508.1, TP512.1
/MCU/MCU_PA5: D501.2 (A), D502.1 (K), J502.8, R507.2, R515.1, TP511.1
/MCU/MCU_PA6: J502.7
/MCU/MCU_PA7: J502.6, R506.1, TP510.1; also elsewhere on the board
/MCU/MCU_PA8: J501.12, TP516.1
/MCU/MCU_PA9: J501.1, R502.1, TP504.1; also elsewhere on the board
/MCU/MCU_PA10: J501.2, R504.2, TP505.1; also elsewhere on the board
/MCU/MCU_PA11: J501.13, TP517.1
/MCU/MCU_PA12: J501.5, TP513.1
/MCU/MCU_PB0: J501.6, TP514.1
/MCU/MCU_PB1: J501.9, TP515.1
/MCU/MCU_PB3: J502.15, TP523.1
/MCU/MCU_PB4: J501.15, R503.1, TP509.1; also elsewhere on the board
/MCU/MCU_PB5: J501.14, R505.2, TP508.1; also elsewhere on the board
/MCU/MCU_PB6: J501.8, R501.2, TP507.1; also elsewhere on the board
/MCU/MCU_PB7: C502.2, J501.7, SW502.2 (B), TP506.1
/MCU/MCU_PC14: J501.10
/MCU/MCU_PC15: J501.11
/MCU/MCU_RST: C501.2, J501.3, J502.3, SW501.2 (B), TP519.1
/MCU/MCU_VIN: J502.1, TP518.1
/MCU/POT_ANA: R508.2; also elsewhere on the board
/NUCLEO DUT/3V3_NUC: R515.2; also elsewhere on the board
GND: C501.1, C502.1, D502.2 (A), D504.2 (A), D505.1 (K), D506.1 (K), D507.1 (K), D508.1 (K), R507.1, R513.2, R514.2, SW501.1 (A), SW502.1 (A), TP501.1; also elsewhere on the board
unnamed: D505.2 (A), R509.2
unnamed: D506.2 (A), R510.2
unnamed: D507.2 (A), R516.2
unnamed: D508.2 (A), R517.2

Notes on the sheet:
250mA max.
EXTI5
connect NUCLEO Tester power to global pwr-nets to power entire device via USB
status LEDs
OR all interrupts of test I/II together
EXTI6
Oscilloscope GND Hook
EXTI7
